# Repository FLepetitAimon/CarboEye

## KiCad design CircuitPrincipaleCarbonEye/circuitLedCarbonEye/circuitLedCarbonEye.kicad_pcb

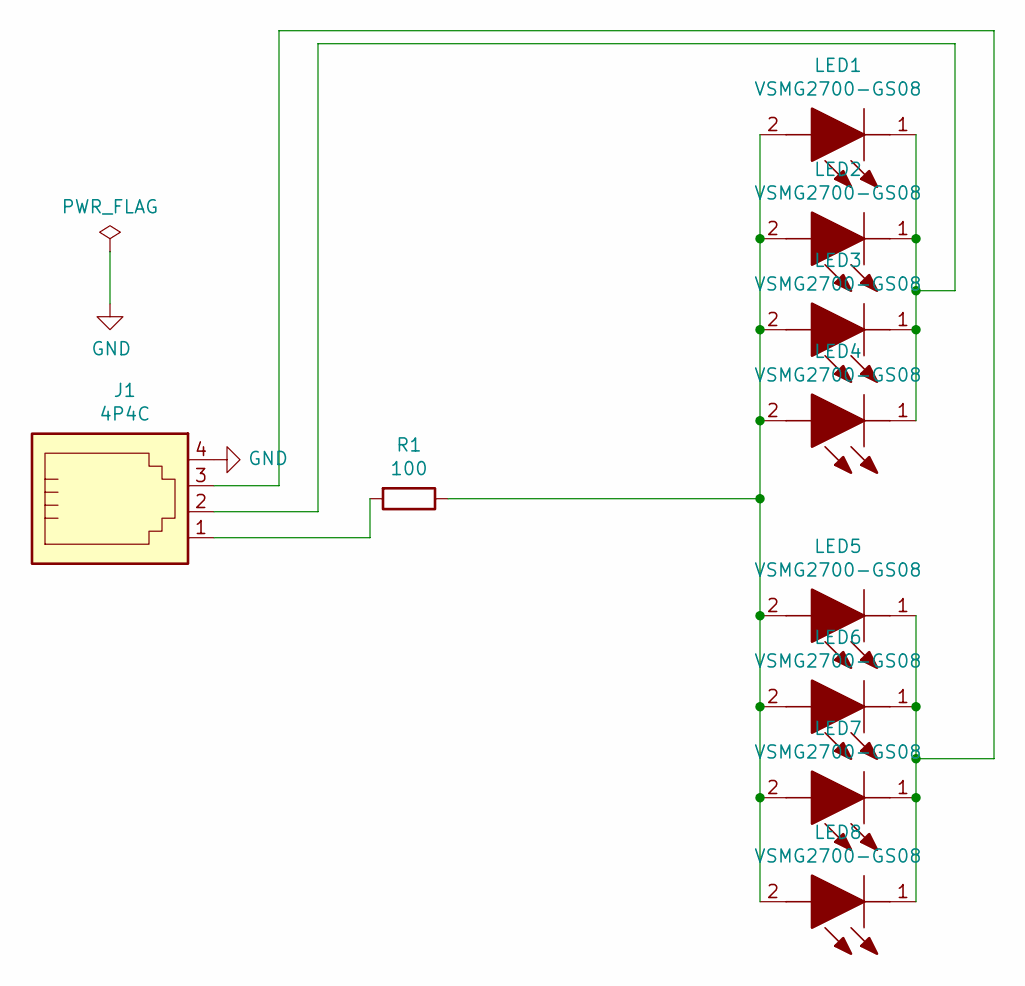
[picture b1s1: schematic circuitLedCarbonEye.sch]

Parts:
J1: 4P4C; Molex_KK-254_AE-6410-04A_1x04_P2.54mm_Vertical
LED1, LED2, LED3, LED4: VSMG2700-GS08; LED_CMS_L4.2mm_W4.2mm; Manufacturer_Part_Number VSMG2700-GS08
LED5, LED6, LED7, LED8: VSMG2700-GS08; LEDM3528X185N; Manufacturer_Part_Number VSMG2700-GS08
R1: 100; R_Axial_DIN0411_L9.9mm_D3.6mm_P12.70mm_Horizontal

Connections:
GND: J1.4
unnamed: J1.1, R1.2
unnamed: J1.2, LED1.1, LED2.1, LED3.1, LED4.1
unnamed: J1.3, LED5.1, LED6.1, LED7.1, LED8.1
unnamed: LED1.2, LED2.2, LED3.2, LED4.2, LED5.2, LED6.2, LED7.2, LED8.2, R1.1

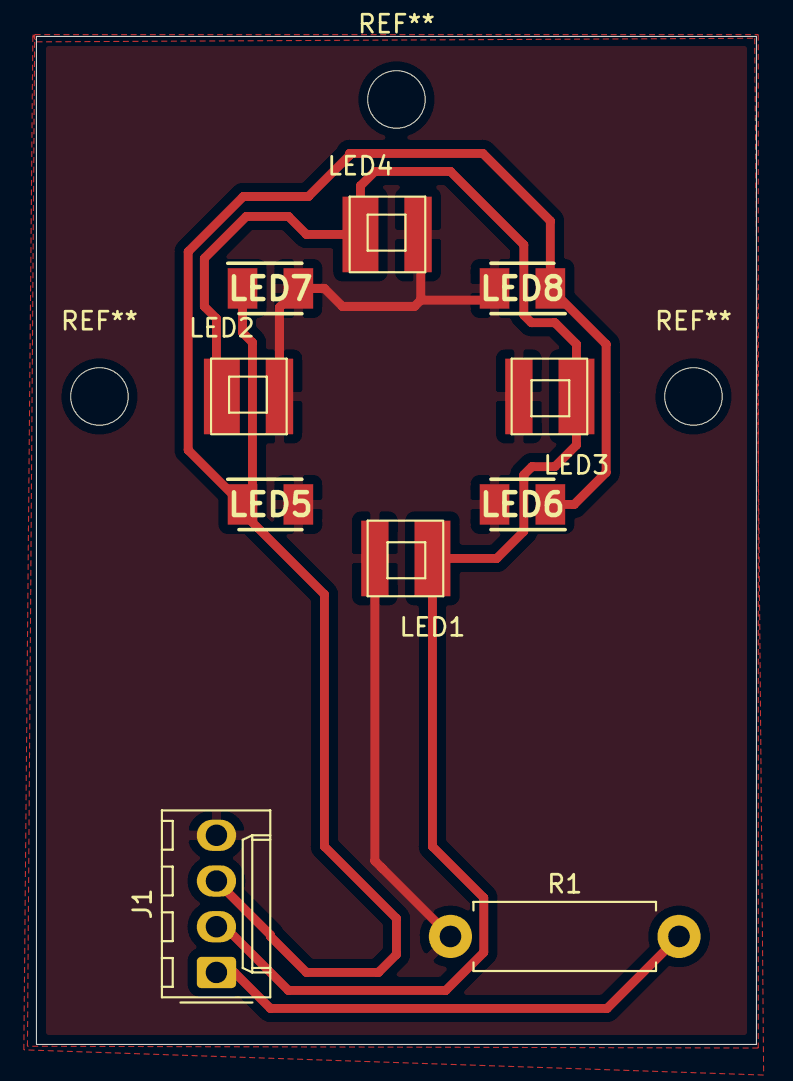
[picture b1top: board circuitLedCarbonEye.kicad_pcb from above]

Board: 2 copper layers, 40.0 x 56.0 mm, 10 parts (0 on the bottom side), 4 nets.

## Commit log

2021-06-25 Initialisation du repertoire
2021-07-06 init
2021-07-09 FreeCAD V2.0
2021-07-09 circuitPrincipaleKiCAD V1.0.1
2021-07-09 KiCAD nettoyage dossier librairie
2021-07-09 merge
2021-07-09 CircuitLed V1.0
2021-07-12 KICAD RoutageCircuit led V1.0
2021-07-12 FreeCAD support photodiode - diamètre 3mm canal
2021-07-15 Mise à jour circuitled et piece 3D pour premiere impression
2021-07-15 mise à jour circuit led pour premiere impresson
2021-07-16 Init programmePrincipale V1.0
2021-07-19 vérification avant impression 1
2021-07-19 ajout fiche technique
2021-07-19 ajout guide d'utilisation
2021-07-27 post premier_test
2021-08-02 adc spi
2021-08-04 ADC 24bits, SPI
2021-08-04 mises à jour fichier stl
2021-08-05 test ad7714 CarbOnFire
2021-08-05 journal de bord 05/08
2021-08-08 test adc
2021-08-09 journal 09/08
2021-08-09 nouveau coefficient pour tension exact
2021-08-10 version double canaux ad7714
2021-08-10 journal de bord 10/08
2021-08-12 12/08
2021-08-17 moyennage = 3
2021-08-19 18/08
2021-08-27 init readme
2022-08-09 rapport
